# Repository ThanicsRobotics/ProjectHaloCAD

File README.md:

# ProjectHaloCAD
This is the official repository of the Thanics Halo open-source project. This is a project powered by the Raspberry Pi Compute Module 3, both the drone and controller use this module, along with several coprocessors. This project is not complete yet and all documaentation has not been uploaded, but feel free to follow along with our progress or use any of our 3D parts or software, as long as you attribute us.
## Background
### The Drone
The Thanics Halo drone utilizes stereo camera vision and ultrasonic sensors to accomplish spherical obstacle avoidance. The Halo drone is built to be versatile with a variety of cameras of different imaging types. The project focuses primarily on 360 (spherical) imaging and spherical video live streaming.

### The Controller
The controller for the Halo drone is equally as innovative as the drone. This is a hybrid controller, able to be used either with two thumbs (traditional), or wrist-mounted for voice or touchscreen control.

## Files
### MCAD Files: 
All mechanical part files for the project (source files are in Fusion 360 archive file .f3d or .f3z)
### ECAD Files: 
All electronics schematics, libraries and Autodesk EAGLE source .sch and .brd files
### Block Diagrams
Higher-level system block diagrams for the Drone and Controller
### Software:
For this project's source code, see our other repository: https://github.com/ThanicsRobotics/ProjectHalo

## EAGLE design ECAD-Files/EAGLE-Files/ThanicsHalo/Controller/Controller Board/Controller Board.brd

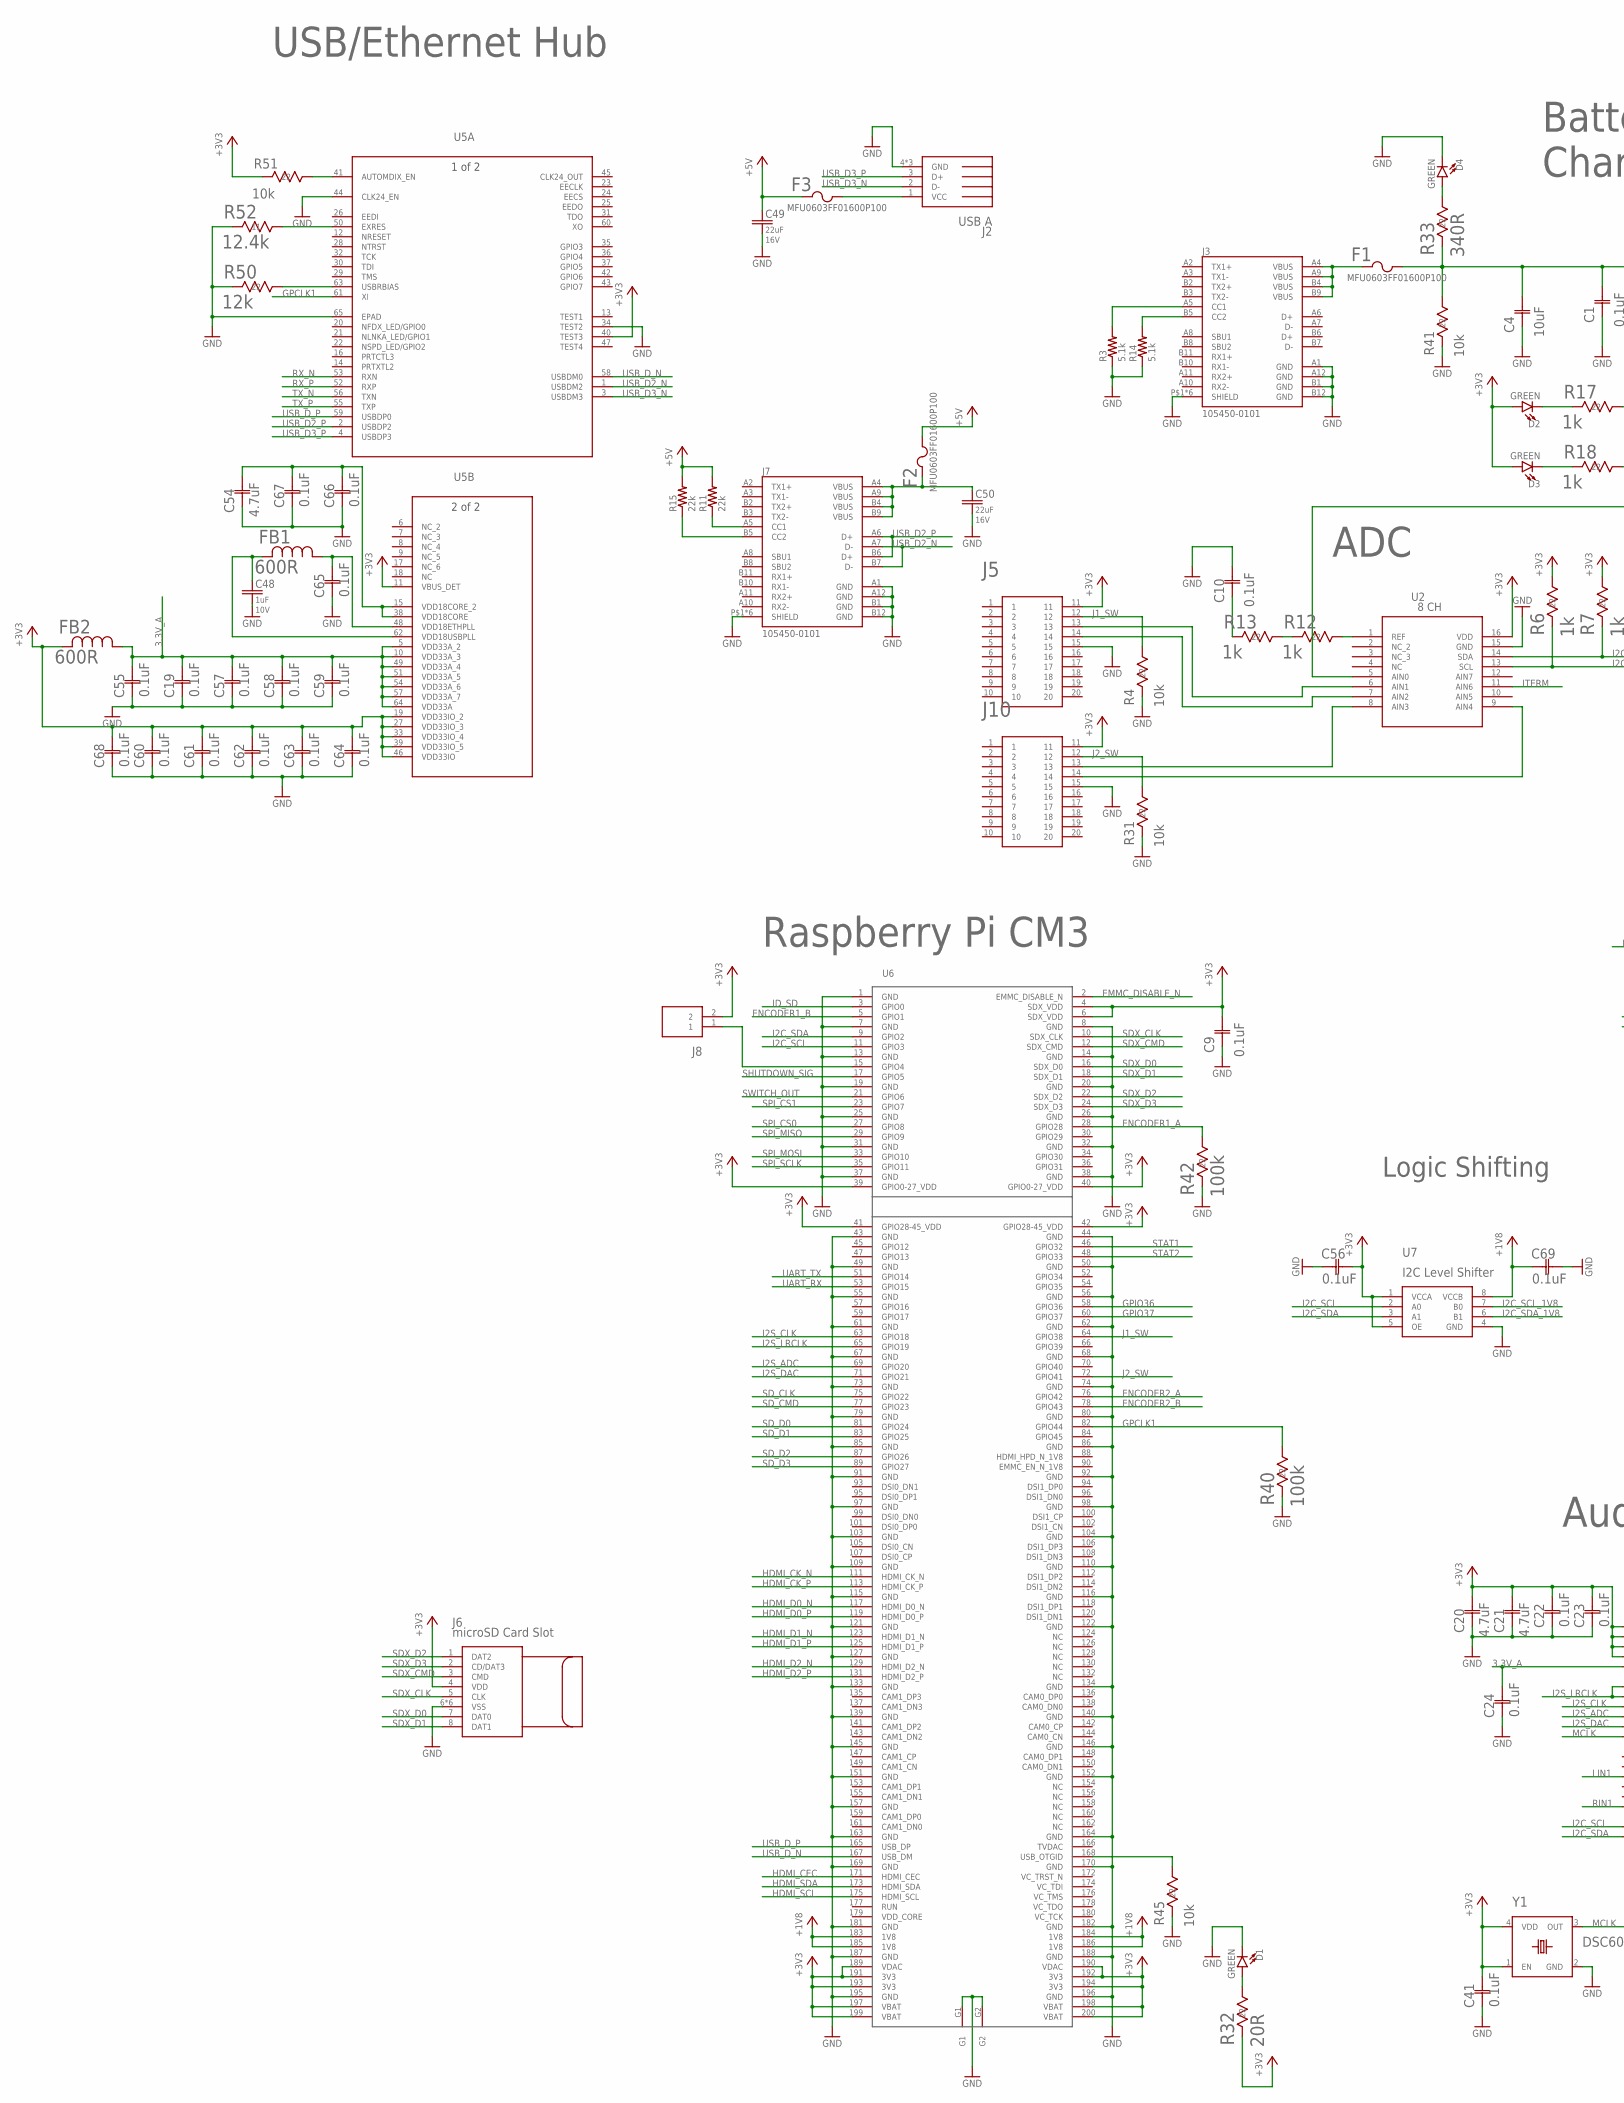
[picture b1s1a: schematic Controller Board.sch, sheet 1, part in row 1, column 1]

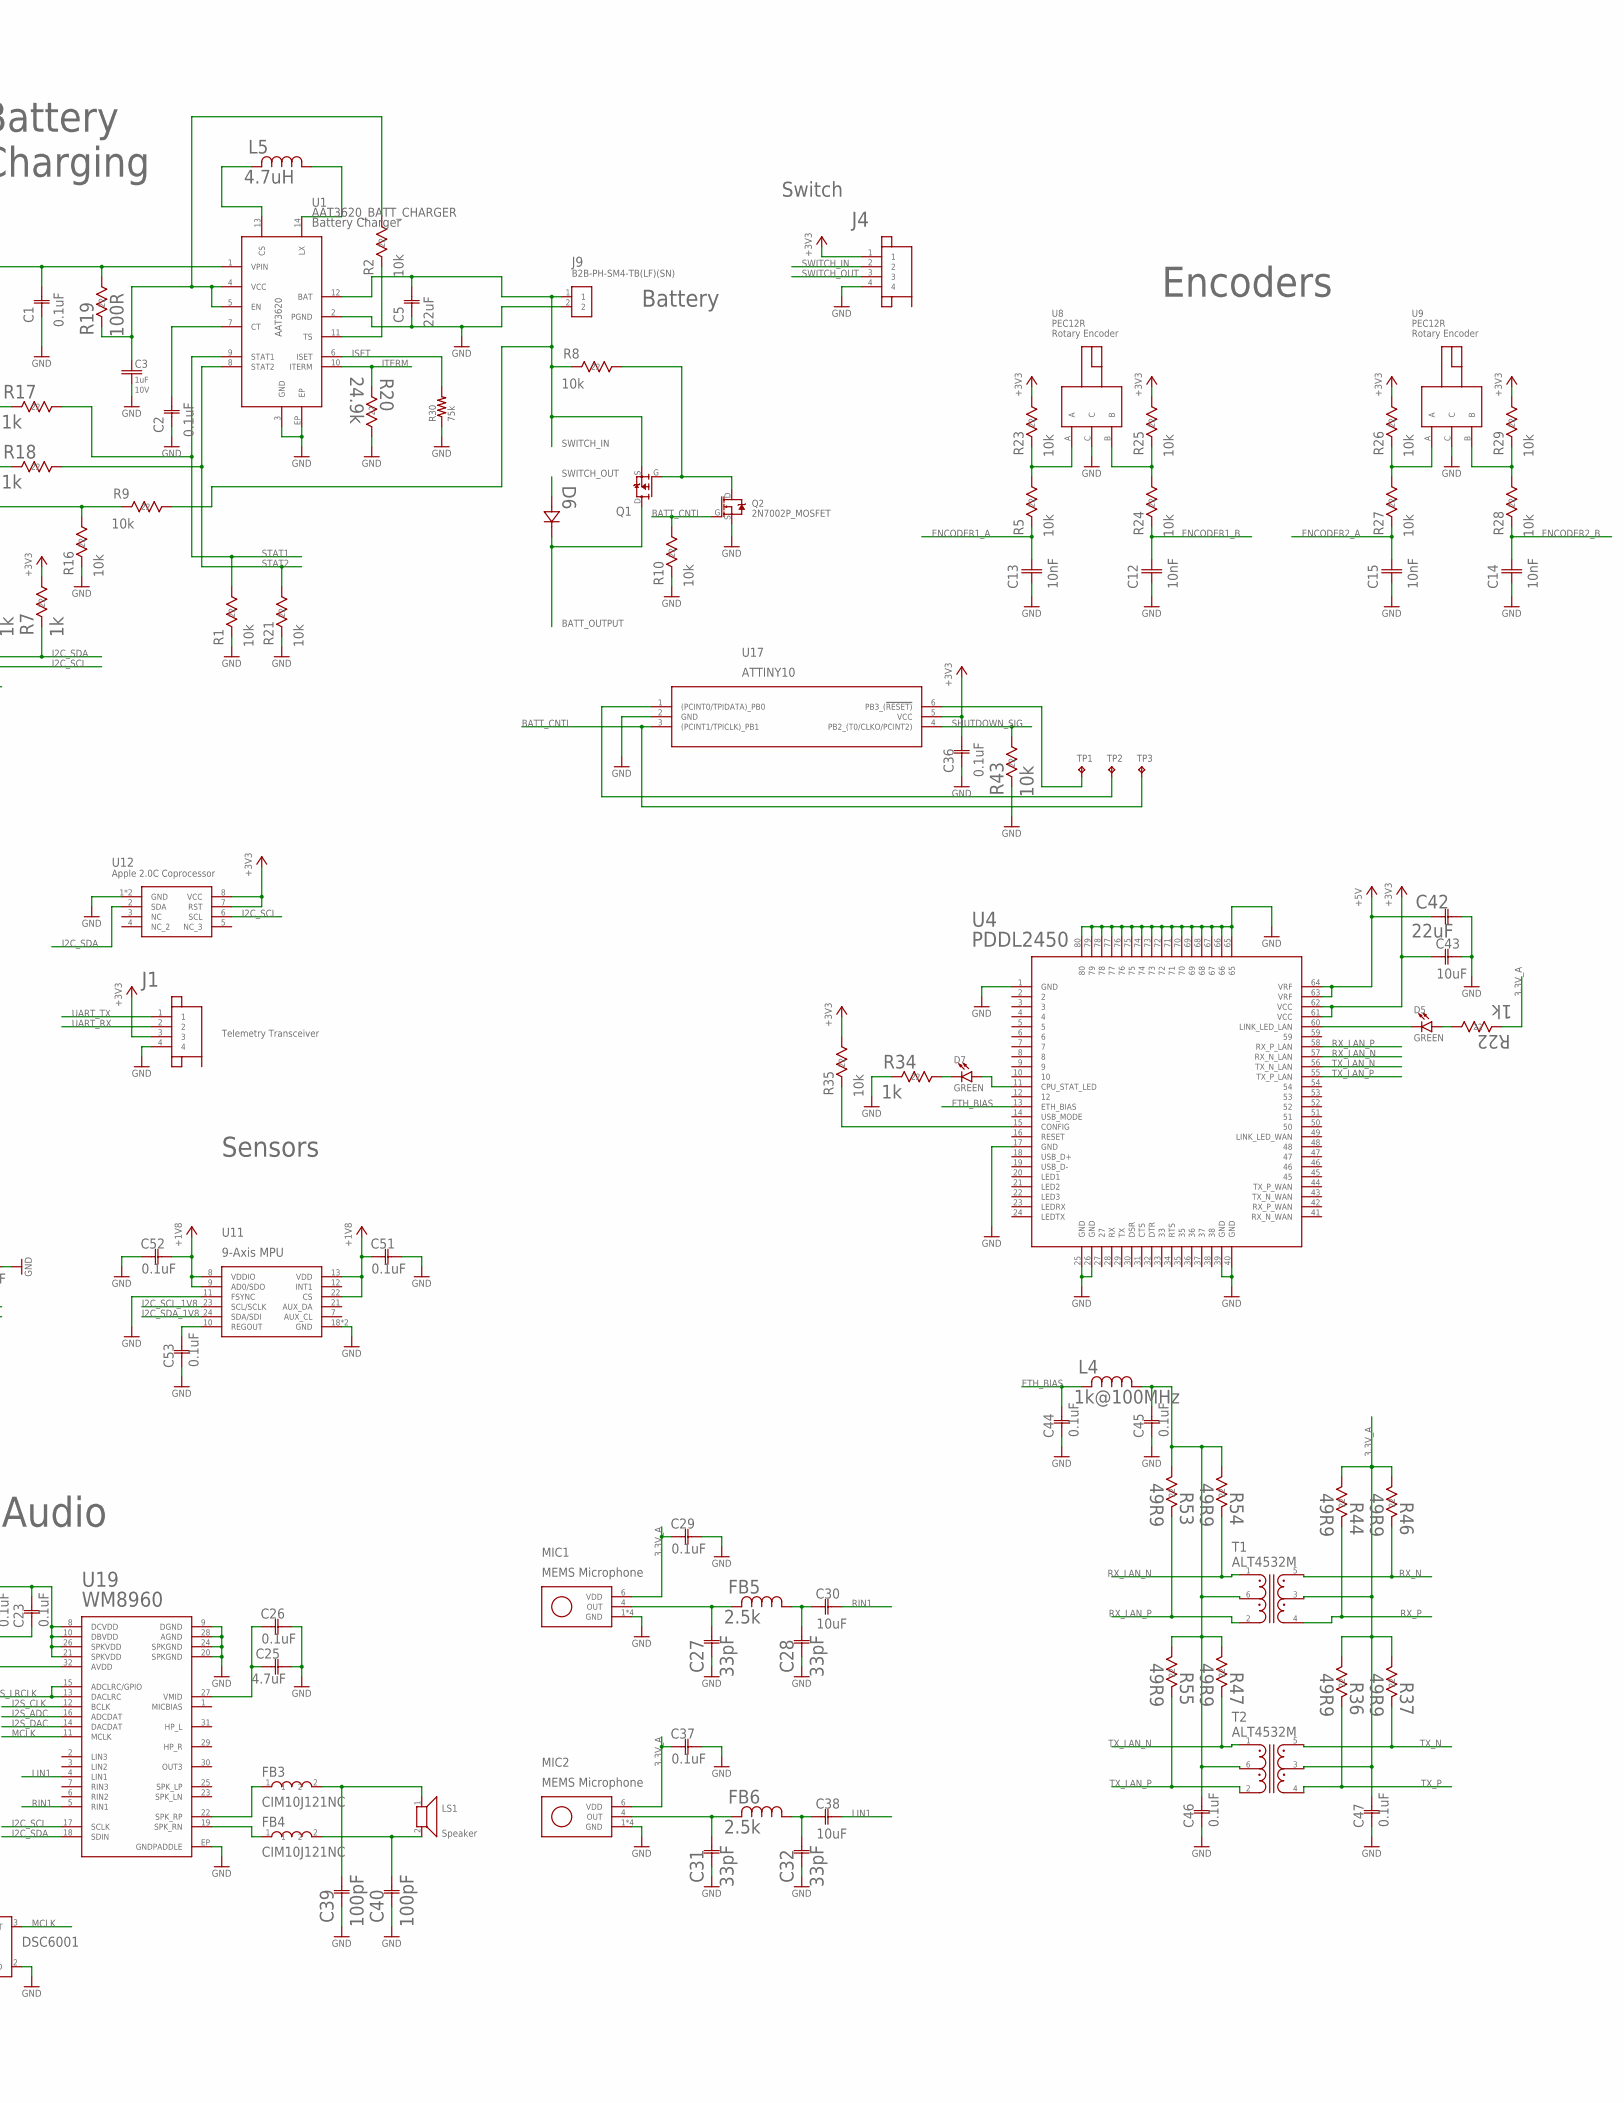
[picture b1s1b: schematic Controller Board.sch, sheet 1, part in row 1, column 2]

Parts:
C1, C2, C9, C10, C36: 0.1uF; 0805
C3, C48: 1uF; C0402
C4, C30, C38, C43: 10uF; G-21
C5, C42: 22uF; G-21
C12, C13, C14, C15: 10nF; 0603_CAPACITOR
C19, C22, C23, C24, C26, C29, C37, C41, C44, C45, C46, C47, C51, C52, C53, C55, C56, C57, C58, C59, C60, C61, C62, C63, C64, C65, C66, C67, C68, C69: 0.1uF; 0402-M
C20, C21, C25, C54: 4.7uF; 0603-M
C27, C28, C31, C32: 33pF; G-155-M
C39, C40: 100pF; YAG_CC0402-M
C49, C50: 22uF; C0805
D1, D2, D3, D4, D5, D7: GREEN; LED-0603
D6: 1N4148W-7-FSOD123-M; SOD123-M
F1, F2, F3: MFU0603FF01600P100; FUS_VISHAY_MFU0603
FB1, FB2: 600R; IND_BLM18_0603-M
FB3, FB4: CIM10J121NC; 0603_CAPACITOR
FB5, FB6: 2.5k; IND_BLM18_0603-M
J1, J4: JST_SH_4POS
J2: USB_A_RECEPT
J3, J7: 105450-0101; MOLEX_105450-0101
J5, J10: EDGE_CONNECTOR_20POS
J6: MICROSD
J8: 2_PIN_CONNECTOR; XH_CONNECTOR
J9: B2B-PH-SM4-TB(LF)(SN)
L4: 1k@100MHz; IND_BLM18_0603-M
L5: 4.7uH; 1008
LS1: SP-1510; SPEAKER
MIC1, MIC2: SPH1642HT5H-1; SISONIC_MICROPHONE
Q1: DMP3099L; SOT-23_(TO-236AB)
Q2: 2N7002P_MOSFET; SOT-23_(TO-236AB)
R1, R2, R4, R5, R8, R9, R10, R16, R21, R23, R24, R25, R26, R27, R28, R29, R31, R35, R41, R45, R51: 10k; RC0603N-M
R3, R14: 5.1k; R0603
R6, R7, R12, R13, R17, R18, R22, R34: 1k; RC0603N-M
R11, R15: 22k; R0603
R19: 100R; RC0603N-M
R20: 24.9k; RC0402N-M
R30: 75k; R0603
R32: 20R; RC0603N-M
R33: 340R; RC0603N
R36, R37, R44, R46, R47, R53, R54, R55: 49R9; RC0402N-M
R40, R42: 100k; RC0603N-M
R43: 10k; RC0805N
R50: 12k; RC0402N-M
R52: 12.4k; YAG_R0402-M
T1, T2: ALT4532M; ALT4532
TP1, TP2, TP3: TPB2,54; B2,54
U1: AAT3620_BATT_CHARGER; AAT3620_TDFN
U2: 8 CH; 21-0055H_16-M
U4: PDDL2450; PDDL2450_SOCKET
U5: LAN9512-JZXQFN64_9X9MC-M; QFN64_9X9MC-M
U6: COMPUTE_MODULE; SO-DIMM
U7: FXMAR2102; 8-UMLP
U8, U9: PEC12R
U11: ICM-20948; QFN40P300X300X105-25N
U12: APPLE_2.0C_COPROCESSOR; PG-USON-8-1
U17: ATTINY10-TSHR6ST1-M; 6ST1-M
U19: WM8960; 32QFN
Y1: DSC6001; 4-VFLGA

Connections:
3.3V_A: C19.2, C24.2, C29.1, C37.1, C47.2, C55.2, C57.2, C58.2, C59.2, FB2.1, MIC1.6 (VDD), MIC2.6 (VDD), R22.2 (22), R36.1 (11), R37.1 (11), R44.1 (11), R46.1 (11), T1.3, T2.3, U5.5 (VDD33A_2), U5.10 (VDD33A_3), U5.49 (VDD33A_4), U5.51 (VDD33A_5), U5.54 (VDD33A_6), U5.57 (VDD33A_7), U5.64 (VDD33A), U19.32 (AVDD)
+1V8: C51.1, C52.2, C69.1, U6.183 (1V8), U6.184 (1V8), U6.185 (1V8), U6.186 (1V8), U7.8 (VCCB), U11.8 (VDDIO), U11.9 (AD0/SDO), U11.13 (VDD), U11.22 (CS); also elsewhere on the board
+3V3: C9.2, C20.2, C21.2, C22.2, C23.2, C36.2, C41.2, C43.1 (11), C56.2, C60.2, C61.2, C62.2, C63.2, C64.2, C68.2, D2.A, D3.A, FB2.2, J1.3, J4.1, J5.11, J6.4 (VDD), J8.2, J10.11, R6.1 (11), R7.1 (11), R23.1 (11), R25.1 (11), R26.1 (11), R29.1 (11), R32.2 (22), R35.1 (11), R51.2 (22), U2.16 (VDD), U4.61 (VCC), U4.62 (VCC), U5.11 (VBUS_DET), U5.19 (VDD33IO_2), U5.27 (VDD33IO_3), U5.33 (VDD33IO_4), U5.39 (VDD33IO_5), U5.40 (TEST3), U5.46 (VDD33IO), U6.4 (SDX_VDD), U6.6 (SDX_VDD), U6.39 (GPIO0-27_VDD), U6.40 (GPIO0-27_VDD), U6.41 (GPIO28-45_VDD), U6.42 (GPIO28-45_VDD), U6.189 (VDAC), U6.190 (VDAC), U6.191 (3V3), U6.192 (3V3), U6.193 (3V3), U6.194 (3V3), U6.197 (VBAT), U6.198 (VBAT), U6.199 (VBAT), U6.200 (VBAT), U7.1 (VCCA), U7.5 (OE), U12.7 (RST), U12.8 (VCC), U17.5 (VCC), U19.8 (DCVDD), U19.10 (DBVDD), U19.21 (SPKVDD), U19.26 (SPKVDD), Y1.1 (EN), Y1.4 (VDD); also elsewhere on the board
+5V: C42.1 (11), C49.1, F2.2, F3.1, R11.2, R15.2, U4.63 (VRF), U4.64 (VRF); also elsewhere on the board
BATT_CNTL: Q2.G, R10.1 (11), TP3.TP, U17.3 ((PCINT1/TPICLK)_PB1)
BATT_OUTPUT: D6.C (12), Q1.D; also elsewhere on the board
EMMC_DISABLE_N: U6.2 (EMMC_DISABLE_N)
ENCODER1_A: C13.2, R5.2 (22), R42.1 (11), U6.28 (GPIO28)
ENCODER1_B: C12.2, R24.2 (22), U6.5 (GPIO1)
ENCODER2_A: C15.2, R27.2 (22), U6.76 (GPIO42)
ENCODER2_B: C14.2, R28.2 (22), U6.78 (GPIO43)
ETH_BIAS: C44.2, L4.2, U4.13 (ETH_BIAS)
GND: C1.1, C2.1, C3.2, C4.1, C5.1, C9.1, C10.2, C12.1, C13.1, C14.1, C15.1, C19.1, C20.1, C21.1, C22.1, C23.1, C24.1, C25.2, C26.2, C27.1 (11), C28.1 (11), C29.2, C31.1 (11), C32.1 (11), C36.1, C37.2, C39.1 (11), C40.1 (11), C41.1, C42.2 (22), C43.2 (22), C44.1, C45.1, C46.1, C47.1, C48.2, C49.2, C50.2, C51.2, C52.1, C53.1, C54.1, C55.1, C56.1, C57.1, C58.1, C59.1, C60.1, C61.1, C62.1, C63.1, C64.1, C65.1, C66.1, C67.1, C68.1, C69.2, D1.C, D4.C, J1.4, J2.4 (GND), J2.5 (GND), J2.6 (GND), J3.A1 (GND), J3.A12 (GND), J3.B1 (GND), J3.B12 (GND), J3.P$1 (SHIELD), J3.P$2 (SHIELD), J3.P$3 (SHIELD), J3.P$4 (SHIELD), J3.P$5 (SHIELD), J3.P$6 (SHIELD), J4.4, J5.15, J6.6 (VSS), J6.9 (VSS), J6.10 (VSS), J6.11 (VSS), J6.12 (VSS), J6.13 (VSS), J7.A1 (GND), J7.A12 (GND), J7.B1 (GND), J7.B12 (GND), J7.P$1 (SHIELD), J7.P$2 (SHIELD), J7.P$3 (SHIELD), J7.P$4 (SHIELD), J7.P$5 (SHIELD), J7.P$6 (SHIELD), J9.2, J10.15, MIC1.1 (GND), MIC1.2 (GND), MIC1.3 (GND), MIC1.5 (GND), MIC2.1 (GND), MIC2.2 (GND), MIC2.3 (GND), MIC2.5 (GND), Q2.S, R1.2 (22), R3.1, R4.2 (22), R10.2 (22), R14.1, R16.2 (22), R20.1 (11), R21.2 (22), R30.1, R31.2 (22), R34.2 (22), R40.2 (22), R41.2 (22), R42.2 (22), R43.2 (22), R45.2 (22), R50.2 (22), R52.1 (11), U1.2 (PGND), U1.3 (GND), U1.EP, U2.15 (GND), U4.1 (GND), U4.17 (GND), U4.25 (GND), U4.26 (GND), U4.39 (GND), U4.40 (GND), U4.65, U4.66, U4.67, U4.68, U4.69, U4.70, U4.71, U4.72, U4.73, U4.74, U4.75, U4.76, U4.77, U4.78, U4.79, U4.80, U5.34 (TEST2), U5.44 (CLK24_EN), U5.65 (EPAD), U6.1 (GND), U6.7 (GND), U6.8 (GND), U6.13 (GND), U6.14 (GND), U6.19 (GND), U6.20 (GND), U6.25 (GND), U6.26 (GND), U6.31 (GND), U6.32 (GND), U6.37 (GND), U6.38 (GND), U6.43 (GND), U6.44 (GND), U6.49 (GND), U6.50 (GND), U6.55 (GND), U6.56 (GND), U6.61 (GND), U6.62 (GND), U6.67 (GND), U6.68 (GND), U6.73 (GND), U6.74 (GND), U6.79 (GND), U6.80 (GND), U6.85 (GND), U6.86 (GND), U6.91 (GND), U6.92 (GND), U6.97 (GND), U6.98 (GND), U6.103 (GND), U6.104 (GND), U6.109 (GND), U6.110 (GND), U6.115 (GND), U6.116 (GND), U6.121 (GND), U6.122 (GND), U6.127 (GND), U6.133 (GND), U6.134 (GND), U6.139 (GND), U6.140 (GND), U6.145 (GND), U6.146 (GND), U6.151 (GND), U6.152 (GND), U6.157 (GND), U6.163 (GND), U6.164 (GND), U6.169 (GND), U6.170 (GND), U6.181 (GND), U6.182 (GND), U6.187 (GND), U6.188 (GND), U6.195 (GND), U6.196 (GND), U6.G1, U6.G2, U7.4 (GND), U8.C, U9.C, U11.11 (FSYNC), U11.18 (GND), U11.20 (GND), U12.1 (GND), U12.9 (GND), U17.2 (GND), U19.9 (DGND), U19.20 (SPKGND), U19.24 (SPKGND), U19.28 (AGND), U19.EP (GNDPADDLE), Y1.2 (GND); also elsewhere on the board
GND2: D5.C, U4.60 (LINK_LED_LAN)
GPCLK1: R40.1 (11), U5.61 (XI), U6.82 (GPIO44)
GPIO36: U6.58 (GPIO36)
GPIO37: U6.60 (GPIO37)
HDMI_CEC: U6.171 (HDMI_CEC)
HDMI_CK_N: U6.111 (HDMI_CK_N)
HDMI_CK_P: U6.113 (HDMI_CK_P)
HDMI_D0_N: U6.117 (HDMI_D0_N)
HDMI_D0_P: U6.119 (HDMI_D0_P)
HDMI_D1_N: U6.123 (HDMI_D1_N)
HDMI_D1_P: U6.125 (HDMI_D1_P)
HDMI_D2_N: U6.129 (HDMI_D2_N)
HDMI_D2_P: U6.131 (HDMI_D2_P)
HDMI_SCL: U6.175 (HDMI_SCL)
HDMI_SDA: U6.173 (HDMI_SDA)
I2C_SCL: R6.2 (22), U2.13 (SCL), U6.11 (GPIO3), U7.2 (A0), U12.6 (SCL), U19.17 (SCLK)
I2C_SCL_1V8: U7.7 (B0), U11.23 (SCL/SCLK)
I2C_SDA: R7.2 (22), U2.14 (SDA), U6.9 (GPIO2), U7.3 (A1), U12.2 (SDA), U19.18 (SDIN)
I2C_SDA_1V8: U7.6 (B1), U11.24 (SDA/SDI)
I2S_ADC: U6.69 (GPIO20), U19.16 (ADCDAT)
I2S_CLK: U6.63 (GPIO18), U19.12 (BCLK)
I2S_DAC: U6.71 (GPIO21), U19.14 (DACDAT)
I2S_LRCLK: U6.65 (GPIO19), U19.13 (DACLRC), U19.15 (ADCLRC/GPIO)
ID_SD: U6.3 (GPIO0)
ISET: R30.2, U1.6 (ISET)
ITERM: R20.2 (22), U1.10 (ITERM), U2.11 (AIN6)
J1_SW: J5.12, R4.1 (11), U6.64 (GPIO38)
J2_SW: J10.12, R31.1 (11), U6.72 (GPIO41)
LIN1: C38.2 (22), U19.4 (LIN1)
MCLK: U19.11 (MCLK), Y1.3 (OUT)
unnamed: TP1.TP, U17.6 (PB3_(!RESET))
unnamed: C2.2, U1.7 (CT)
unnamed: L5.P$2 (2), U1.13 (CS)
unnamed: L5.P$1 (1), U1.14 (LX)
unnamed: C3.1, R2.1 (11), R19.2 (22), U1.4 (VCC), U1.5 (EN)
unnamed: C53.2, U11.10 (REGOUT)
unnamed: D4.A, R33.1 (11)
unnamed: D1.A, R32.1 (11)
unnamed: R2.2 (22), U1.11 (TS)
unnamed: C25.1, C26.1, U19.27 (VMID)
unnamed: D2.C, R17.2 (22)
unnamed: R12.1 (11), U2.1 (REF)
unnamed: J5.13, U2.6 (AIN1)
unnamed: J5.14, U2.7 (AIN2)
unnamed: J10.13, U2.8 (AIN3)
unnamed: J10.14, U2.9 (AIN4)
unnamed: C27.2 (22), FB5.2, MIC1.4 (OUT)
unnamed: D3.C, R18.2 (22)
unnamed: R12.2 (22), R13.1 (11)
unnamed: C10.1, R13.2 (22)
unnamed: R5.1 (11), R23.2 (22), U8.A
unnamed: C28.2 (22), C30.1 (11), FB5.1
unnamed: R24.1 (11), R25.2 (22), U8.B
unnamed: C31.2 (22), FB6.2, MIC2.4 (OUT)
unnamed: C32.2 (22), C38.1 (11), FB6.1
unnamed: R26.2 (22), R27.1 (11), U9.A
unnamed: R28.1 (11), R29.2 (22), U9.B
unnamed: R9.2 (22), R16.1 (11), U2.5 (AIN0)
unnamed: FB4.1, U19.19 (SPK_RN)
unnamed: FB3.1, U19.22 (SPK_RP)
unnamed: C39.2 (22), FB3.2, LS1.1
unnamed: C40.2 (22), FB4.2, LS1.2
unnamed: J3.B5 (CC2), R14.2
unnamed: F1.1, J3.A4 (VBUS), J3.A9 (VBUS), J3.B4 (VBUS), J3.B9 (VBUS)
unnamed: J3.A5 (CC1), R3.2
unnamed: J7.A5 (CC1), R11.1
unnamed: C50.1, F2.1, J7.A4 (VBUS), J7.A9 (VBUS), J7.B4 (VBUS), J7.B9 (VBUS)
unnamed: R45.1 (11), U6.168 (USB_OTGID)
unnamed: J8.1, U6.15 (GPIO4)
unnamed: R51.1 (11), U5.41 (AUTOMDIX_EN)
unnamed: R50.1 (11), U5.63 (USBRBIAS)
unnamed: Q1.G, Q2.D, R8.1 (11)
unnamed: C65.2, FB1.1, U5.48 (VDD18ETHPLL)
unnamed: C48.1, FB1.2, U5.62 (VDD18USBPLL)
unnamed: R52.2 (22), U5.50 (EXRES)
unnamed: C54.2, C66.2, C67.2, U5.15 (VDD18CORE_2), U5.38 (VDD18CORE)
unnamed: J7.B5 (CC2), R15.1
unnamed: D5.A, R22.1 (11)
unnamed: R35.2 (22), U4.15 (CONFIG)
unnamed: D7.A, U4.11 (CPU_STAT_LED)
unnamed: D7.C, R34.1 (11)
unnamed: C45.2, C46.2, L4.1, R47.1 (11), R53.1 (11), R54.1 (11), R55.1 (11), T1.6, T2.6
unnamed: F3.2, J2.1 (VCC)
PB0: TP2.TP, U17.1 ((PCINT0/TPIDATA)_PB0)
RIN1: C30.2 (22), U19.5 (RIN1)
RX_LAN_N: R54.2 (22), T1.1, U4.57 (RX_N_LAN)
RX_LAN_P: R53.2 (22), T1.2, U4.58 (RX_P_LAN)
RX_N: R46.2 (22), T1.5, U5.53 (RXN)
RX_P: R44.2 (22), T1.4, U5.52 (RXP)
SDX_CLK: J6.5 (CLK), U6.10 (SDX_CLK)
SDX_CMD: J6.3 (CMD), U6.12 (SDX_CMD)
SDX_D0: J6.7 (DAT0), U6.16 (SDX_D0)
SDX_D1: J6.8 (DAT1), U6.18 (SDX_D1)
SDX_D2: J6.1 (DAT2), U6.22 (SDX_D2)
SDX_D3: J6.2 (CD/DAT3), U6.24 (SDX_D3)
SD_CLK: U6.75 (GPIO22)
SD_CMD: U6.77 (GPIO23)
SD_D0: U6.81 (GPIO24)
SD_D1: U6.83 (GPIO25)
SD_D2: U6.87 (GPIO26)
SD_D3: U6.89 (GPIO27)
SHUTDOWN_SIG: R43.1 (11), U6.17 (GPIO5), U17.4 (PB2_(T0/CLKO/PCINT2))
SPI_CS0: U6.27 (GPIO8)
SPI_CS1: U6.23 (GPIO7)
SPI_MISO: U6.29 (GPIO9)
SPI_MOSI: U6.33 (GPIO10)
SPI_SCLK: U6.35 (GPIO11)
STAT1: R1.1 (11), R17.1 (11), U1.9 (STAT1), U6.46 (GPIO32)
STAT2: R18.1 (11), R21.1 (11), U1.8 (STAT2), U6.48 (GPIO33)
SWITCH_IN: C5.2, J4.2, J9.1, Q1.S, R8.2 (22), R9.1 (11), U1.12 (BAT)
SWITCH_OUT: D6.A (21), J4.3, U6.21 (GPIO6)
TX_LAN_N: R47.2 (22), T2.1, U4.56 (TX_N_LAN)
TX_LAN_P: R55.2 (22), T2.2, U4.55 (TX_P_LAN)
TX_N: R37.2 (22), T2.5, U5.56 (TXN)
TX_P: R36.2 (22), T2.4, U5.55 (TXP)
UART_RX: J1.2, U6.53 (GPIO15)
UART_TX: J1.1, U6.51 (GPIO14)
USB_5V: C1.2, C4.2, F1.2, R19.1 (11), R33.2 (22), R41.1 (11), U1.1 (VPIN)
USB_D2_N: J7.A7 (D-), J7.B7 (D-), U5.1 (USBDM2)
USB_D2_P: J7.A6 (D+), J7.B6 (D+), U5.2 (USBDP2)
USB_D3_N: J2.2 (D-), U5.3 (USBDM3)
USB_D3_P: J2.3 (D+), U5.4 (USBDP3)
USB_D_N: U5.58 (USBDM0), U6.167 (USB_DM)
USB_D_P: U5.59 (USBDP0), U6.165 (USB_DP)

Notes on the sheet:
Battery
Switch
Telemetry Transceiver
Battery Charging
USB/Ethernet Hub
Encoders
Audio
ADC
Raspberry Pi CM3
Sensors
Logic Shifting

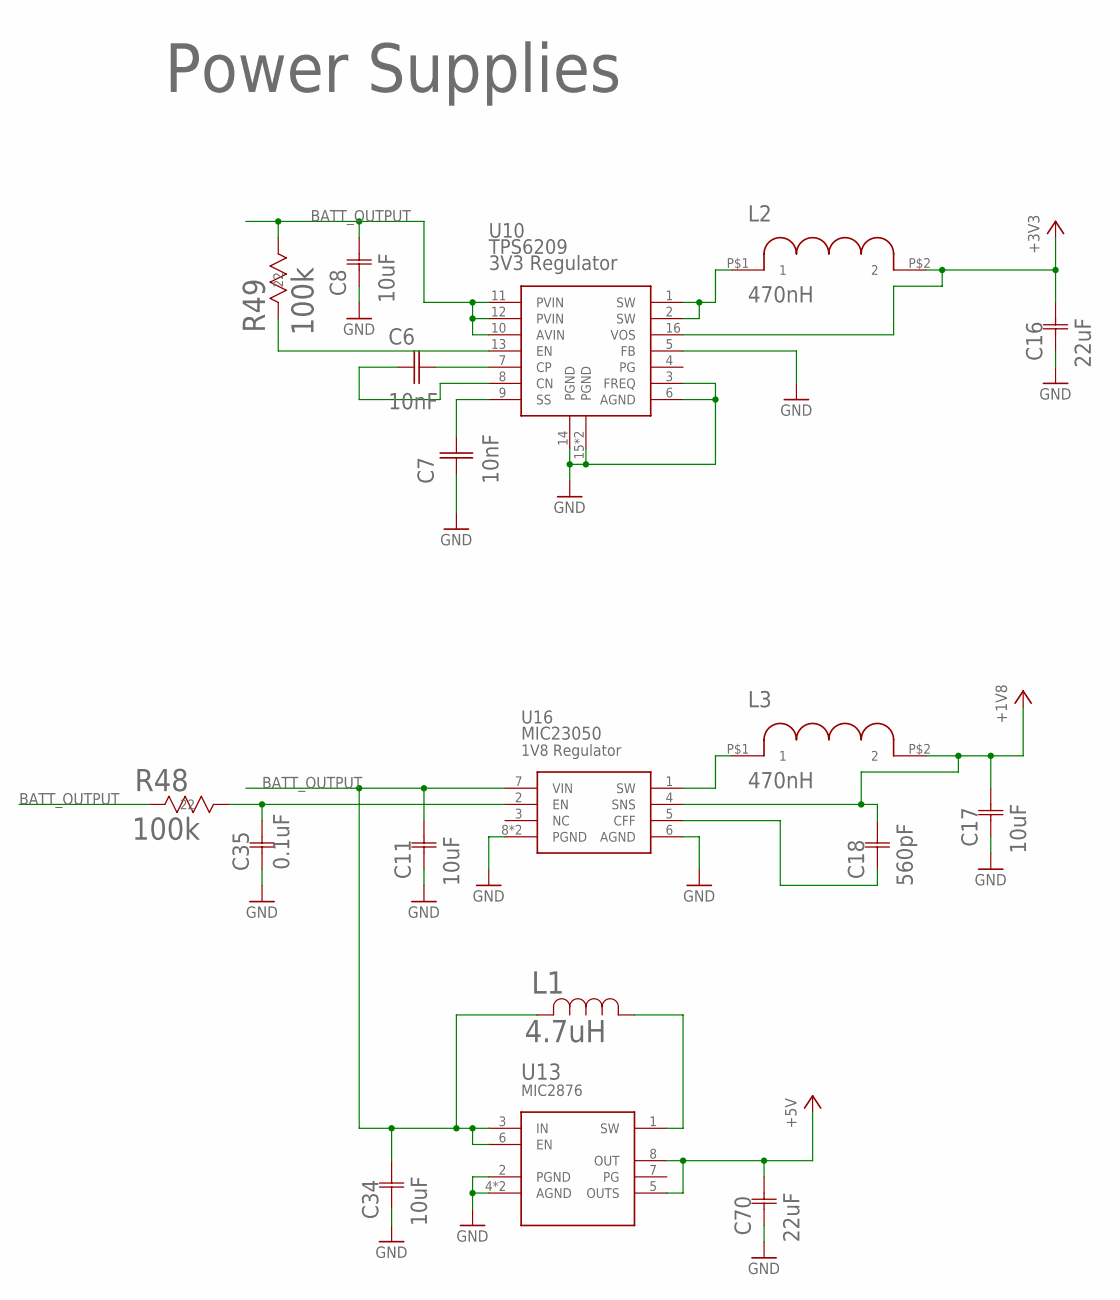
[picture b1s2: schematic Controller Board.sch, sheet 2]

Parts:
C6, C7: 10nF; 0603_CAPACITOR
C8, C11, C17, C34: 10uF; G-21
C16, C70: 22uF; G-21
C18: 560pF; CC0402N-M
C35: 0.1uF; 0402-M
L1: 4.7uH; 1008
L2, L3: 470nH; 470NH_INDUCTOR
R48, R49: 100k; RC0603N-M
U10: TPS6209; VQFN16
U13: MIC2876UDFN-8; UDFN8
U16: MIC23050; MLF(ML)_8PIN

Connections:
+1V8: C17.2, C18.2, L3.P$2 (2), U16.4 (SNS); also elsewhere on the board
+3V3: C16.2, L2.P$2 (2), U10.16 (VOS); also elsewhere on the board
+5V: C70.2, U13.5 (OUTS), U13.8 (OUT); also elsewhere on the board
BATT_OUTPUT: C8.2, C11.2, C34.2, L1.P$2 (2), R48.2 (22), R49.1 (11), U10.10 (AVIN), U10.11 (PVIN), U10.12 (PVIN), U13.3 (IN), U13.6 (EN), U16.7 (VIN); also elsewhere on the board
GND: C7.1, C8.1, C11.1, C16.1, C17.1, C34.1, C35.1, C70.1, U10.3 (FREQ), U10.5 (FB), U10.6 (AGND), U10.14 (PGND), U10.15 (PGND), U10.17 (PGND), U13.2 (PGND), U13.4 (AGND), U13.EP (AGND), U16.6 (AGND), U16.8 (PGND), U16.EP (PGND); also elsewhere on the board
unnamed: R49.2 (22), U10.13 (EN)
unnamed: C35.2, R48.1 (11), U16.2 (EN)
unnamed: C6.2, U10.7 (CP)
unnamed: C6.1, U10.8 (CN)
unnamed: C7.2, U10.9 (SS)
unnamed: L2.P$1 (1), U10.1 (SW), U10.2 (SW)
unnamed: L3.P$1 (1), U16.1 (SW)
unnamed: C18.1, U16.5 (CFF)
unnamed: L1.P$1 (1), U13.1 (SW)

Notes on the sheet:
Power Supplies

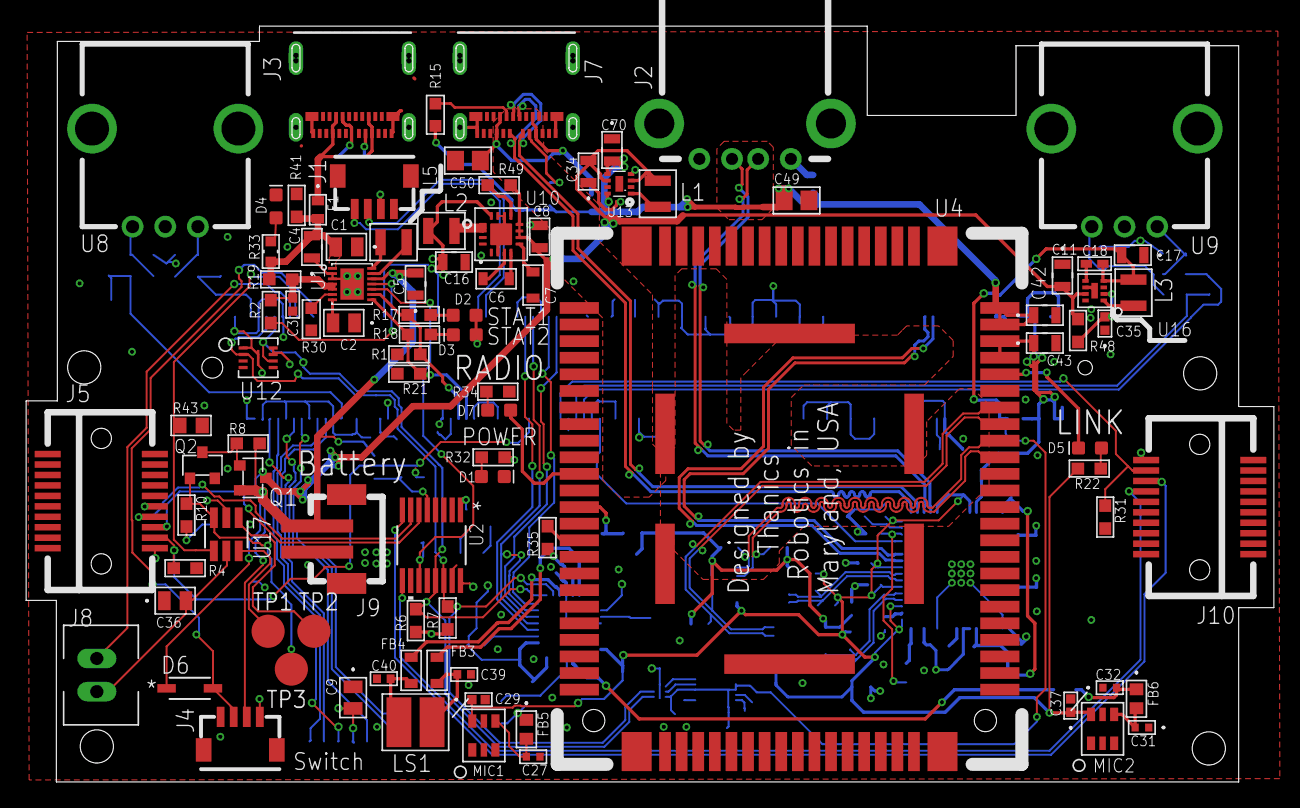
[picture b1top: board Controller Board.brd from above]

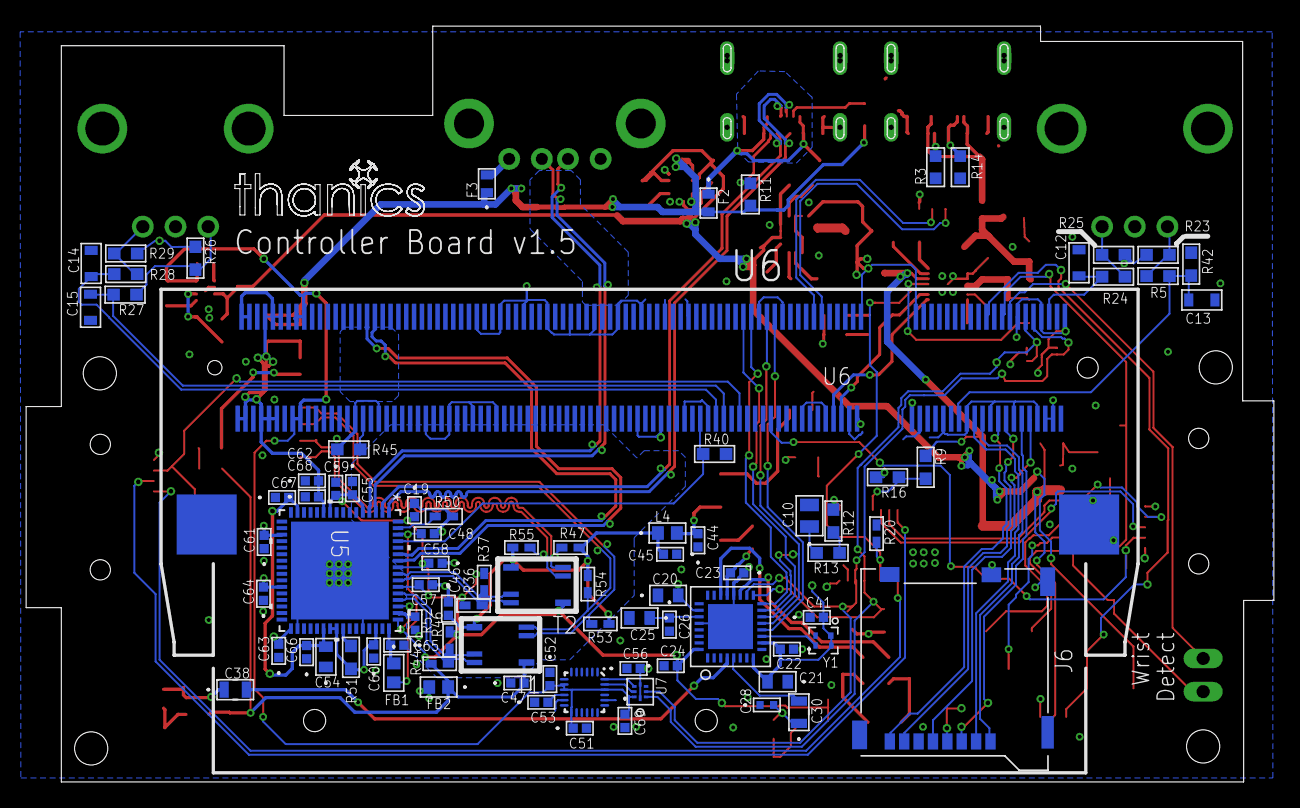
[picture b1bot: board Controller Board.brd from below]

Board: 4 copper layers, 95.5 x 57.8 mm, 179 parts (85 on the bottom side), 120 nets.

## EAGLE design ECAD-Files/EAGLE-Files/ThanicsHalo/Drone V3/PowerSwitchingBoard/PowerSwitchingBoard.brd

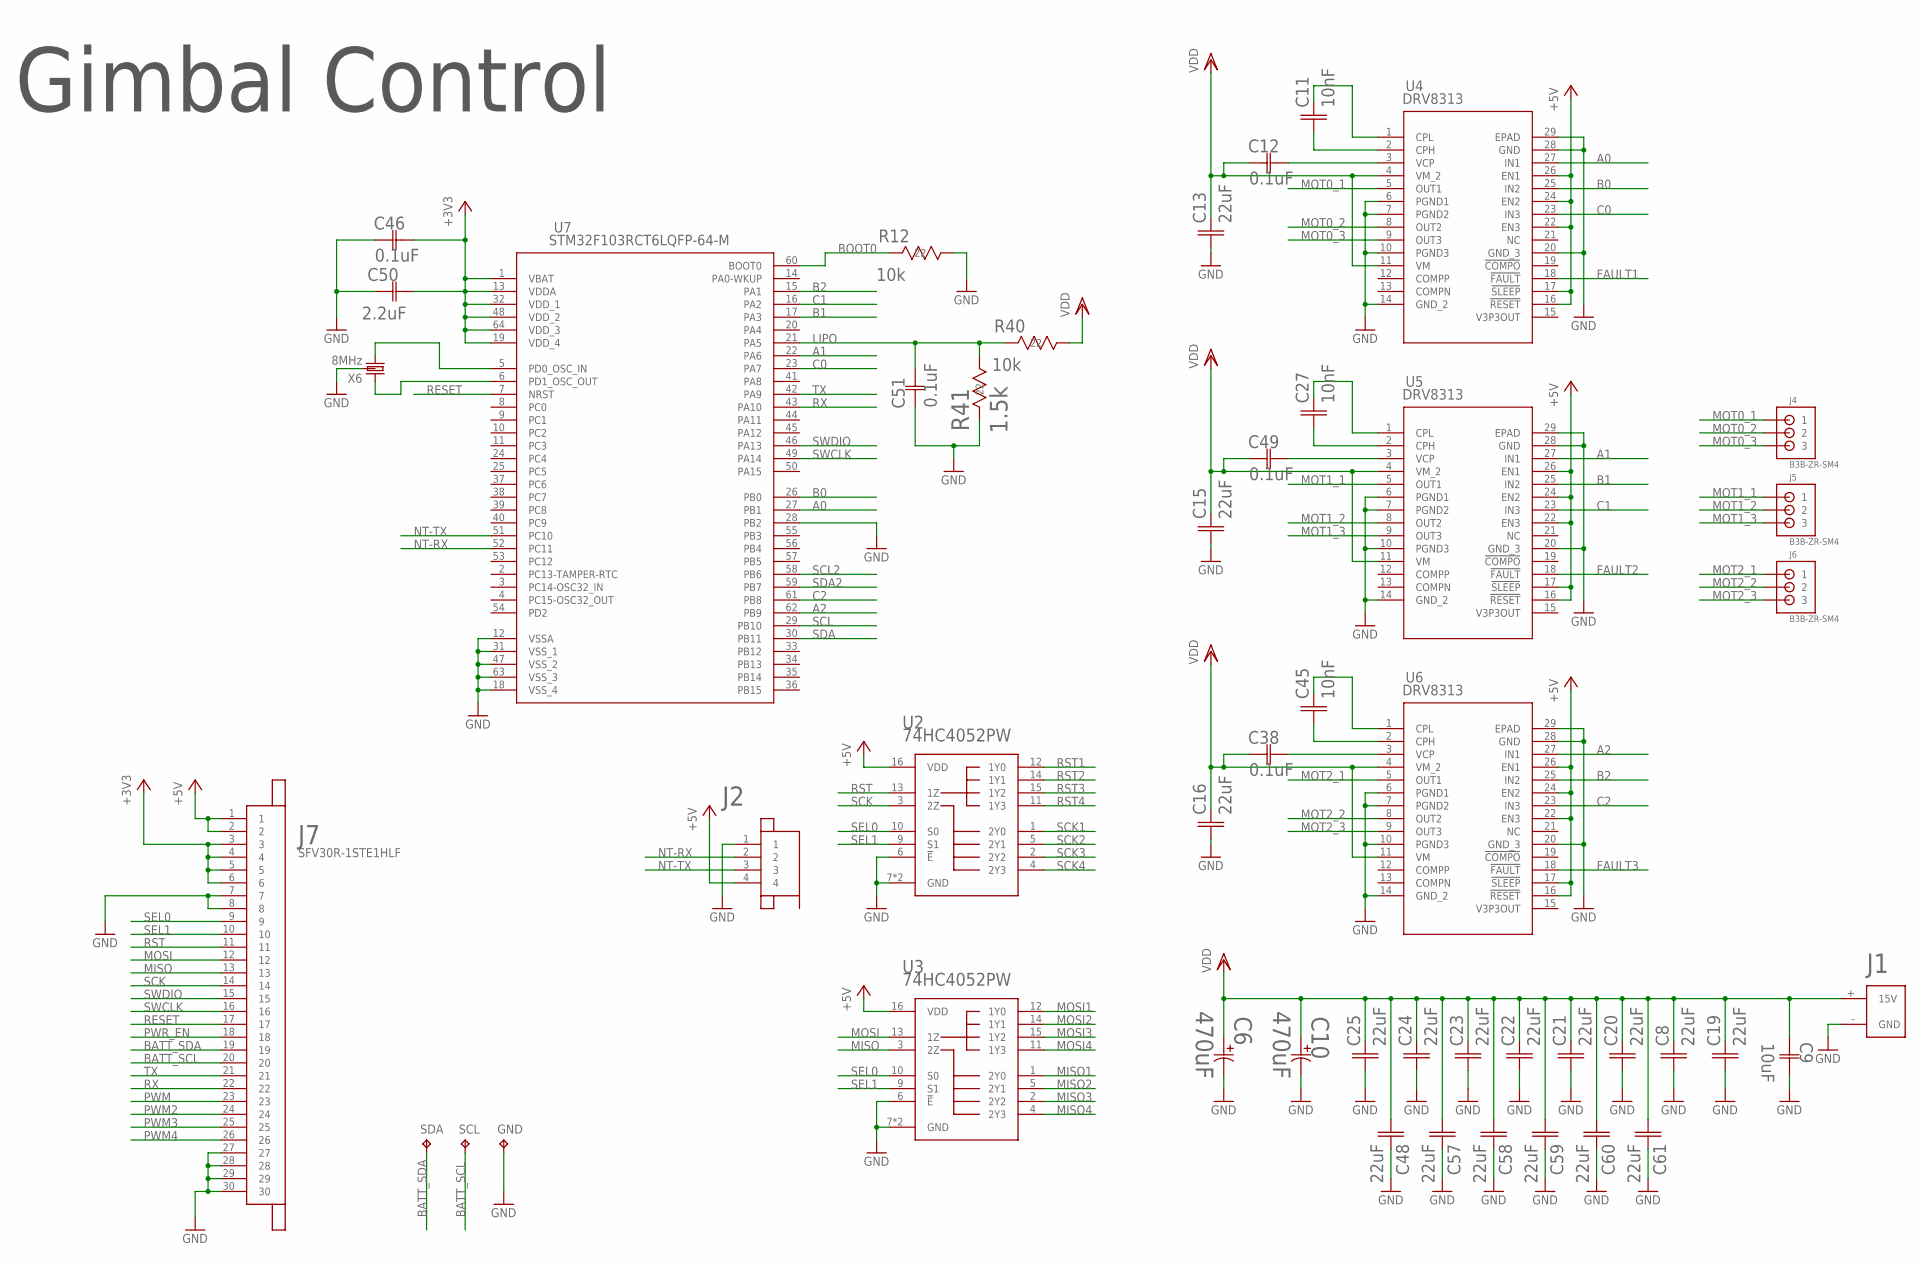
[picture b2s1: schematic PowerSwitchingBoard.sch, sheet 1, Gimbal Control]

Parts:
C6, C10: 470uF; PCAP_10X10-ELECT-M
C8, C13, C15, C16, C19, C20, C21, C22, C23, C24, C25, C48, C57, C58, C59, C60, C61: 22uF; 1210_CAPACITOR
C9: 10uF; G-21
C11, C27, C45: 10nF; 0603_CAPACITOR
C12, C38, C46, C49, C51: 0.1uF; 0402-M
C50: 2.2uF; G-188-M
GND: TPTP20SQ; TP20SQ
J1: ESC_CONTACTS; XT60_CONNECTOR
J2: JST_SH_4POS
J4, J5, J6: B3B-ZR-SM4
J7: SFV30R-1STE1HLF
R12, R40: 10k; RC0603N-M
R41: 1.5k; RC0603N-M
SCL: TPTP20SQ; TP20SQ
SDA: TPTP20SQ; TP20SQ
U2, U3: 74HC4052PW; TSSOP16
U4, U5, U6: DRV8313; PWP28_5P18X3P1-M
U7: STM32F103RCT6LQFP-64-M; LQFP-64-M
X6: 8MHz; 3-SMD

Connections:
+3V3: C46.2, C50.2 (22), J7.3, J7.4, J7.5, J7.6, U7.1 (VBAT), U7.13 (VDDA), U7.19 (VDD_4), U7.32 (VDD_1), U7.48 (VDD_2), U7.64 (VDD_3); also elsewhere on the board
+5V: J2.4, J7.1, J7.2, U2.16 (VDD), U3.16 (VDD), U4.16 (!RESET), U4.17 (!SLEEP), U4.22 (EN3), U4.24 (EN2), U4.26 (EN1), U5.16 (!RESET), U5.17 (!SLEEP), U5.22 (EN3), U5.24 (EN2), U5.26 (EN1), U6.16 (!RESET), U6.17 (!SLEEP), U6.22 (EN3), U6.24 (EN2), U6.26 (EN1); also elsewhere on the board
A0: U4.27 (IN1), U7.27 (PB1)
A1: U5.27 (IN1), U7.22 (PA6)
A2: U6.27 (IN1), U7.62 (PB9)
B0: U4.25 (IN2), U7.26 (PB0)
B1: U5.25 (IN2), U7.17 (PA3)
B2: U6.25 (IN2), U7.15 (PA1)
BATT_SCL: J7.20, SCL.TP
BATT_SDA: J7.19, SDA.TP
BOOT0: R12.2 (22), U7.60 (BOOT0)
C0: U4.23 (IN3), U7.23 (PA7)
C1: U5.23 (IN3), U7.16 (PA2)
C2: U6.23 (IN3), U7.61 (PB8)
FAULT1: U4.18 (!FAULT)
FAULT2: U5.18 (!FAULT)
FAULT3: U6.18 (!FAULT)
GND: C6.2 (22), C8.1, C9.2 (22), C10.2 (22), C13.1, C15.1, C16.1, C19.1, C20.1, C21.1, C22.1, C23.1, C24.1, C25.1, C46.1, C48.2, C50.1 (11), C51.1, C57.2, C58.2, C59.2, C60.2, C61.2, GND.TP, J1.- (GND), J2.1, J7.7, J7.8, J7.27, J7.28, J7.29, J7.30, R12.1 (11), R41.2 (22), U2.6 (!E), U2.7 (GND), U2.8 (GND), U3.6 (!E), U3.7 (GND), U3.8 (GND), U4.6 (PGND1), U4.7 (PGND2), U4.10 (PGND3), U4.14 (GND_2), U4.20 (GND_3), U4.28 (GND), U4.29 (EPAD), U5.6 (PGND1), U5.7 (PGND2), U5.10 (PGND3), U5.14 (GND_2), U5.20 (GND_3), U5.28 (GND), U5.29 (EPAD), U6.6 (PGND1), U6.7 (PGND2), U6.10 (PGND3), U6.14 (GND_2), U6.20 (GND_3), U6.28 (GND), U6.29 (EPAD), U7.12 (VSSA), U7.18 (VSS_4), U7.28 (PB2), U7.31 (VSS_1), U7.47 (VSS_2), U7.63 (VSS_3), X6.2 (GND); also elsewhere on the board
LIPO: C51.2, R40.2 (22), R41.1 (11), U7.21 (PA5)
MISO: J7.13, U3.3 (2Z)
MISO1: U3.1 (2Y0); also elsewhere on the board
MISO2: U3.5 (2Y1); also elsewhere on the board
MISO3: U3.2 (2Y2); also elsewhere on the board
MISO4: U3.4 (2Y3); also elsewhere on the board
MOSI: J7.12, U3.13 (1Z)
MOSI1: U3.12 (1Y0); also elsewhere on the board
MOSI2: U3.14 (1Y1); also elsewhere on the board
MOSI3: U3.15 (1Y2); also elsewhere on the board
MOSI4: U3.11 (1Y3); also elsewhere on the board
MOT0_1: J4.1, U4.5 (OUT1)
MOT0_2: J4.2, U4.8 (OUT2)
MOT0_3: J4.3, U4.9 (OUT3)
MOT1_1: J5.1, U5.5 (OUT1)
MOT1_2: J5.2, U5.8 (OUT2)
MOT1_3: J5.3, U5.9 (OUT3)
MOT2_1: J6.1, U6.5 (OUT1)
MOT2_2: J6.2, U6.8 (OUT2)
MOT2_3: J6.3, U6.9 (OUT3)
unnamed: C11.1, U4.2 (CPH)
unnamed: C11.2, U4.1 (CPL)
unnamed: C27.1, U5.2 (CPH)
unnamed: C27.2, U5.1 (CPL)
unnamed: C49.2, U5.3 (VCP)
unnamed: C45.1, U6.2 (CPH)
unnamed: C45.2, U6.1 (CPL)
unnamed: C38.2, U6.3 (VCP)
unnamed: U7.5 (PD0_OSC_IN), X6.3 (2)
unnamed: C12.2, U4.3 (VCP)
unnamed: U7.6 (PD1_OSC_OUT), X6.1
NT-RX: J2.2, U7.52 (PC11)
NT-TX: J2.3, U7.51 (PC10)
PWM: J7.23; also elsewhere on the board
PWM2: J7.24; also elsewhere on the board
PWM3: J7.25; also elsewhere on the board
PWM4: J7.26; also elsewhere on the board
PWR_EN: J7.18; also elsewhere on the board
RESET: J7.17, U7.7 (NRST)
RST: J7.11, U2.13 (1Z)
RST1: U2.12 (1Y0); also elsewhere on the board
RST2: U2.14 (1Y1); also elsewhere on the board
RST3: U2.15 (1Y2); also elsewhere on the board
RST4: U2.11 (1Y3); also elsewhere on the board
RX: J7.22, U7.43 (PA10)
SCK: J7.14, U2.3 (2Z)
SCK1: U2.1 (2Y0); also elsewhere on the board
SCK2: U2.5 (2Y1); also elsewhere on the board
SCK3: U2.2 (2Y2); also elsewhere on the board
SCK4: U2.4 (2Y3); also elsewhere on the board
SCL: U7.29 (PB10)
SCL2: U7.58 (PB6)
SDA: U7.30 (PB11)
SDA2: U7.59 (PB7)
SEL0: J7.9, U2.10 (S0), U3.10 (S0)
SEL1: J7.10, U2.9 (S1), U3.9 (S1)
SWCLK: J7.16, U7.49 (PA14)
SWDIO: J7.15, U7.46 (PA13)
TX: J7.21, U7.42 (PA9)
VDD: C6.1 (11), C8.2, C9.1 (11), C10.1 (11), C12.1, C13.2, C15.2, C16.2, C19.2, C20.2, C21.2, C22.2, C23.2, C24.2, C25.2, C38.1, C48.1, C49.1, C57.1, C58.1, C59.1, C60.1, C61.1, J1.+ (15V), R40.1 (11), U4.4 (VM_2), U4.11 (VM), U5.4 (VM_2), U5.11 (VM), U6.4 (VM_2), U6.11 (VM); also elsewhere on the board

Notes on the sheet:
Gimbal Control

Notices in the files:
parts and their libraries:
COPYRIGHT: Copyright C 2015 Accelerated Designs. All rights reserved
SparkFun-LED: Licensing: Creative Commons ShareAlike 4.0 International - https://creativecommons.org/licenses/by-sa/4.0
